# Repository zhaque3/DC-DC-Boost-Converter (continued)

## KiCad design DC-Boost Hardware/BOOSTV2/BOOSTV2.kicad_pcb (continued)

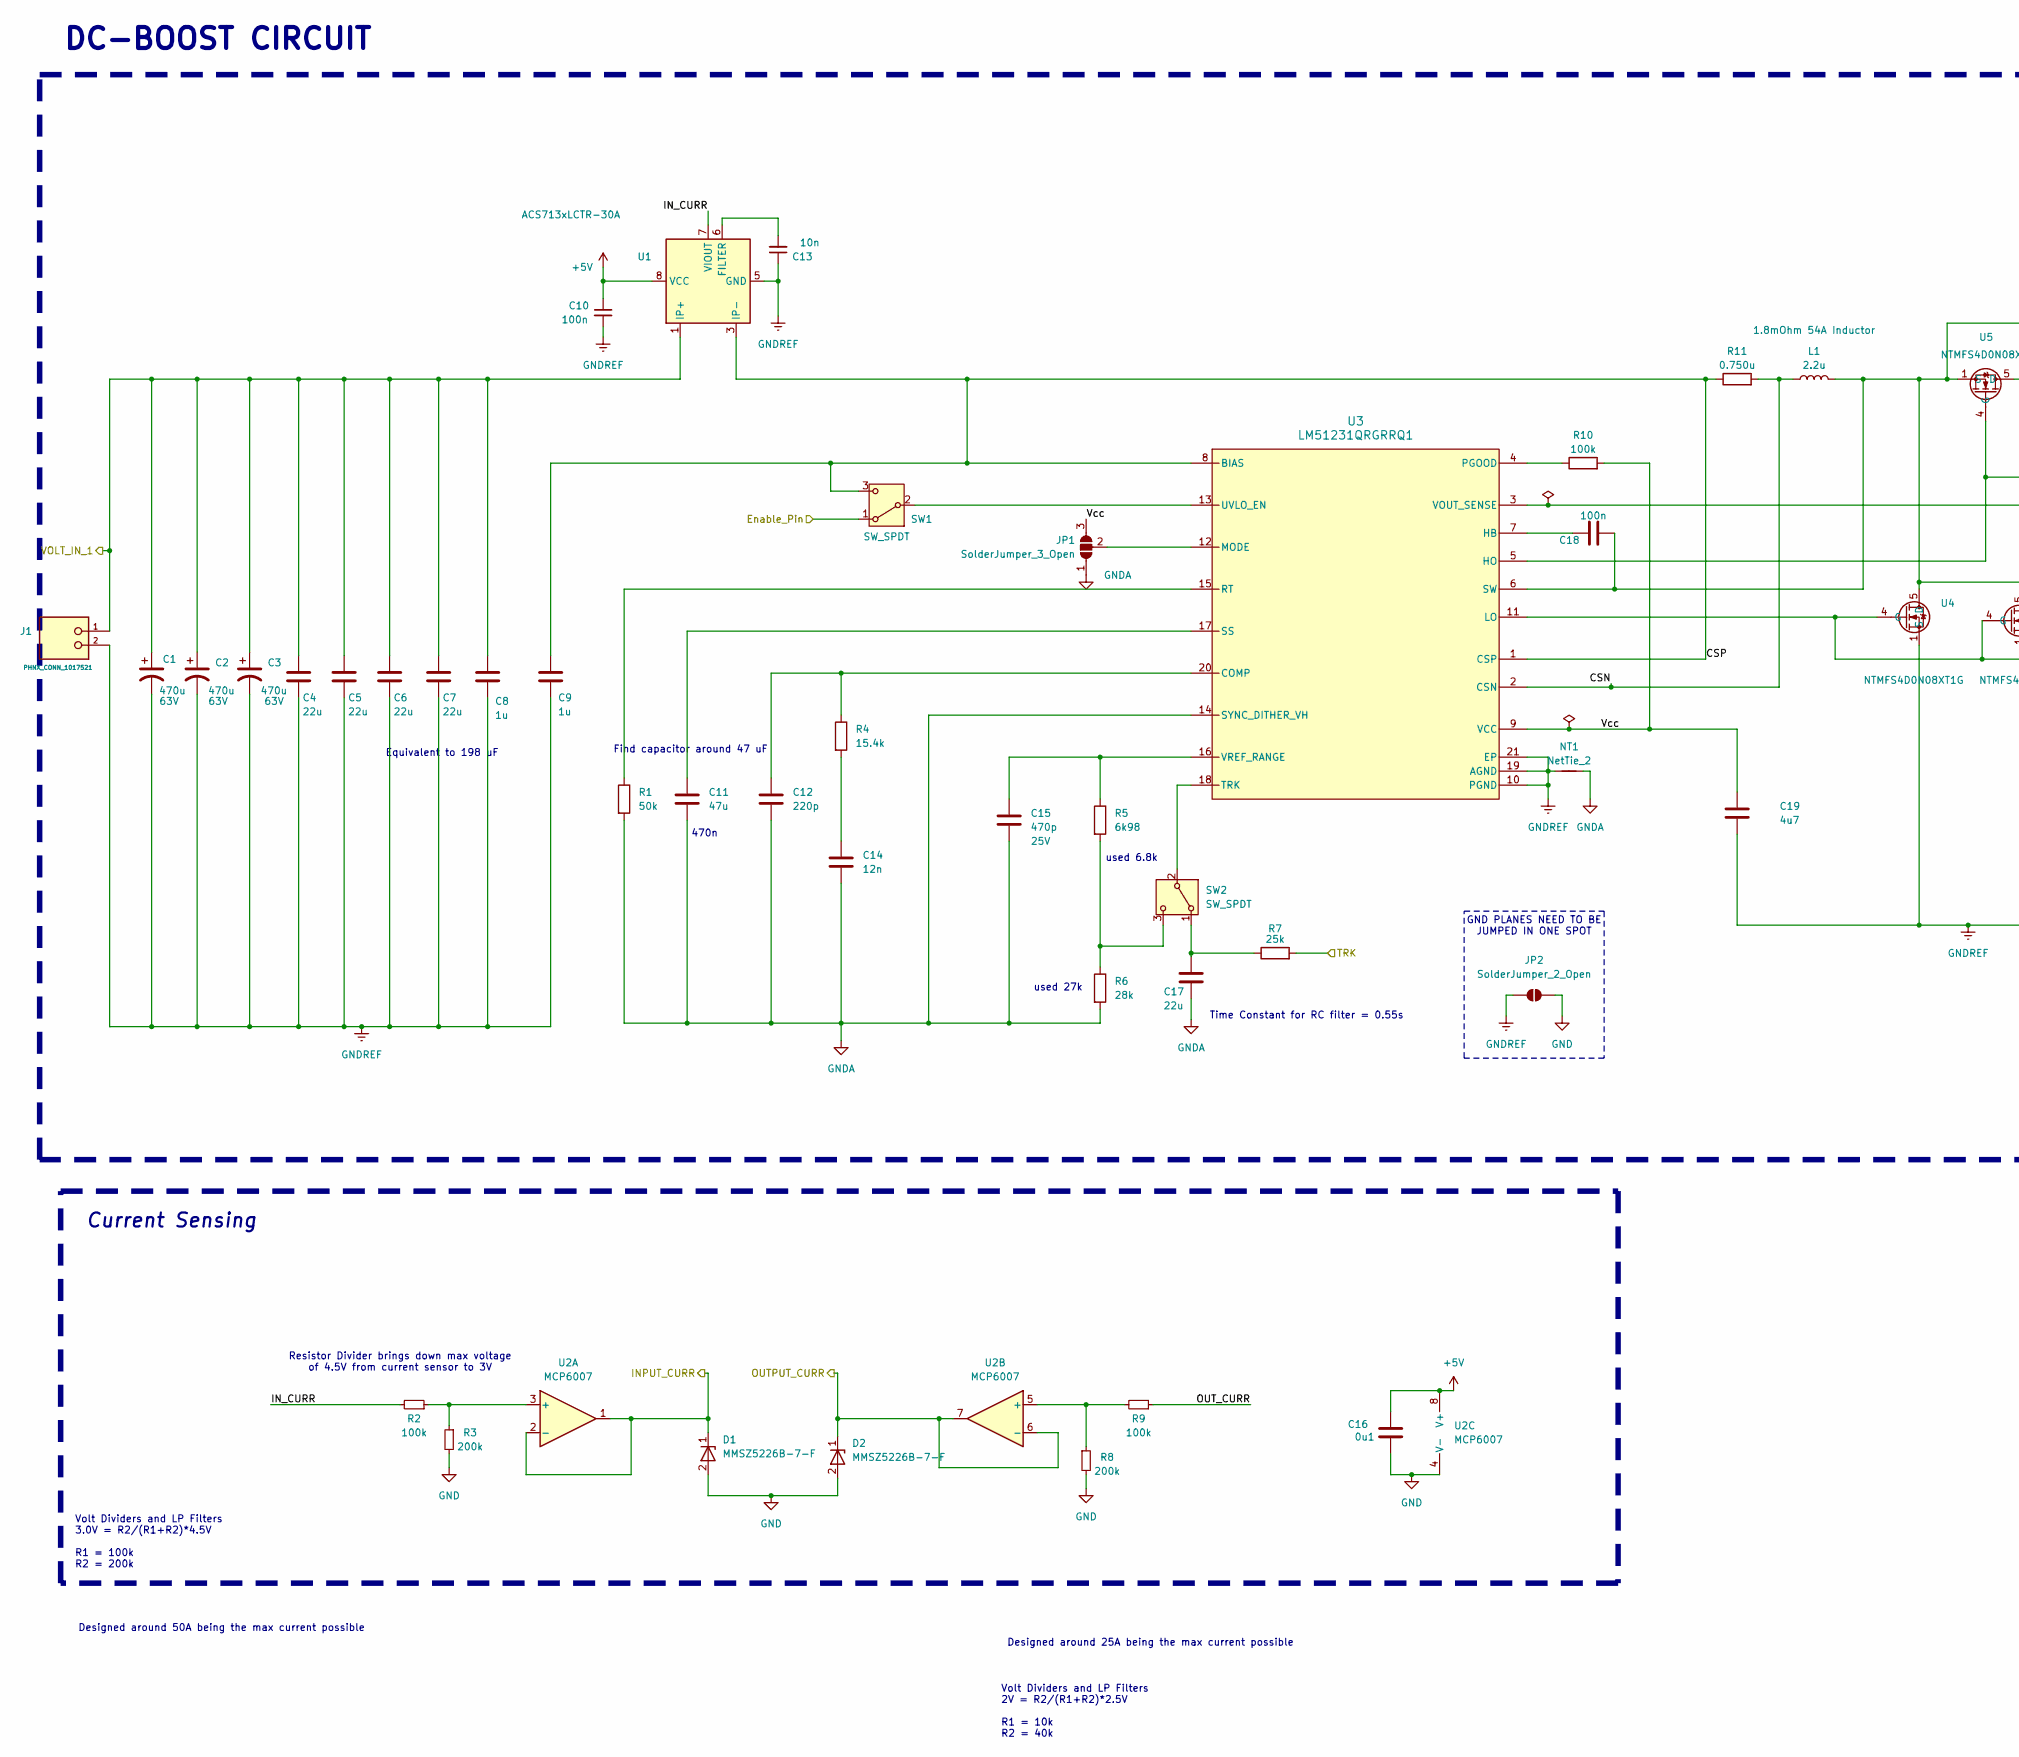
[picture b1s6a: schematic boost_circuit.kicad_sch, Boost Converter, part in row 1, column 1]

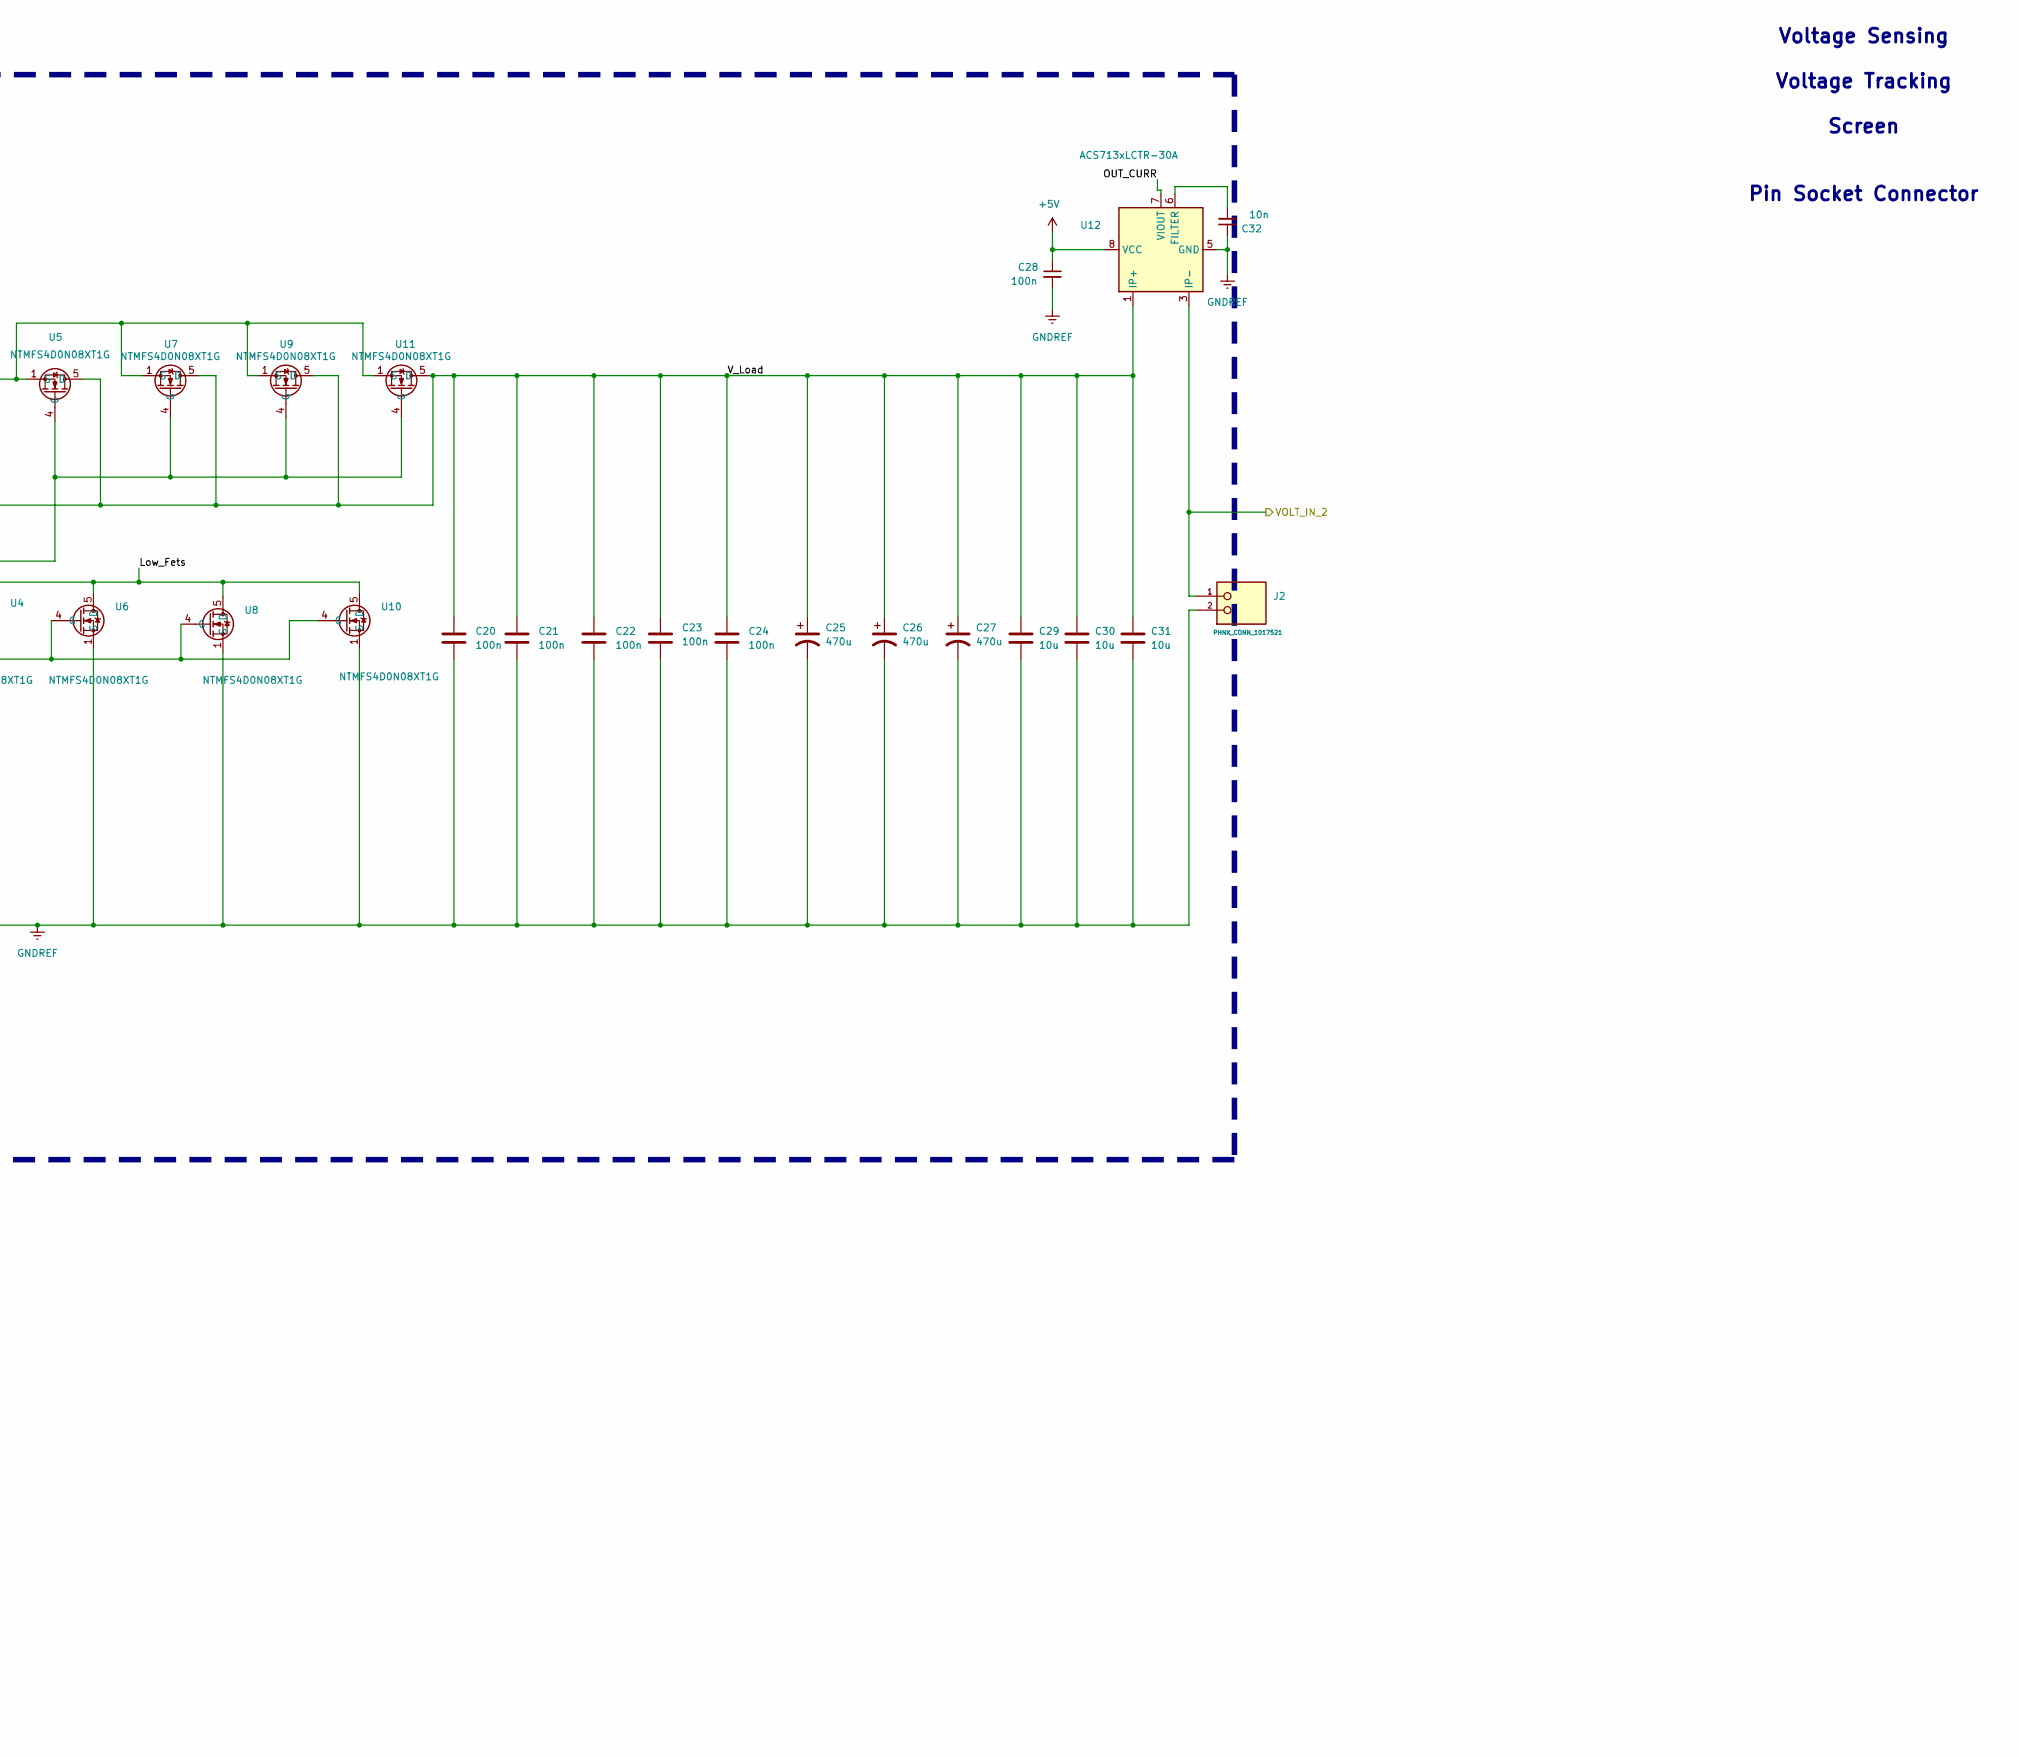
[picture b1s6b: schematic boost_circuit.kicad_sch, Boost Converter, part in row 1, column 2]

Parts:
C1, C2, C3: 470u; CAP_PAN_10X20_PAN; Part # ECA-1HM471B
C4, C5, C6, C7: 22u; C_0805_2012Metric
C8, C9: 1u; C_0603_1608Metric
C10, C28: 100n; C_0603_1608Metric; Part# C88219
C11: 47u; C_0603_1608Metric
C12: 220p; C_0805_2012Metric
C13, C32: 10n; C_0603_1608Metric; Part# C88219
C14: 12n; C_0603_1608Metric
C15: 470p; C_0603_1608Metric; Rating 25V
C16: 0u1; C_0603_1608Metric
C17: 22u; C_0603_1608Metric
C18: 100n; R_0603_1608Metric
C19: 4u7; C_0603_1608Metric
C20, C21, C22, C23, C24: 100n; C_0603_1608Metric
C25, C26, C27: 470u; CAP_YX_16X31P5_RUB; Part # 100ZLH470MEFC16X31.5
C29, C30, C31: 10u; C_1210_3225Metric
D1, D2: MMSZ5226B-7-F; D_SOD_123_M; Part# C155250
J1, J2: PHNX_CONN_1017521; PHOENIX_1017521; PARTREV 04.01.2018
JP1: SolderJumper_3_Open; SolderJumper-3_P1.3mm_Open_RoundedPad1.0x1.5mm_NumberLabels
JP2: SolderJumper_2_Open; SolderJumper-2_P1.3mm_Open_RoundedPad1.0x1.5mm
L1: 2.2u; L_Kemet_3u3
NT1: NetTie_2; NetTie-2_SMD_Pad0.5mm
R1: 50k; R_0603_1608Metric
R2, R9, R10: 100k; R_0603_1608Metric
R3: 200k; R_0603_1608Metric; Part# C25811
R4: 15.4k; R_0603_1608Metric_Pad0.98x0.95mm_HandSolder
R5: 6k98; R_0603_1608Metric
R6: 28k; R_0603_1608Metric
R7: 25k; R_0603_1608Metric
R8: 200k; R_0603_1608Metric
R11: 0.750u; CSS2H3920RL700F
SW1, SW2: SW_SPDT; PinHeader_1x03_P2.54mm_Vertical
U1, U12: ACS713xLCTR-30A; SOIC-8_3.9x4.9mm_P1.27mm
U2: MCP6007; SOIC-8_3.9x4.9mm_P1.27mm
U3: LM51231QRGRRQ1; RGR0020C-MFG
U4, U5, U6, U7, U8, U9, U10, U11: NTMFS4D0N08XT1G; PowerMosDFNHybrid

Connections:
+5V: C10.1, C16.1, C28.1, U1.8 (VCC), U2.8 (V+), U12.8 (VCC); also elsewhere on the board
/Boost-Circuit/CSN: L1.1, R11.2, U3.2 (CSN)
/Boost-Circuit/CSP: C9.1, R11.1, SW1.3 (C), U1.3 (IP-), U1.4 (IP-), U3.1 (CSP), U3.8 (BIAS)
/Boost-Circuit/Enable_Pin: SW1.1 (A); also elsewhere on the board
/Boost-Circuit/INPUT_CURR: D1.1, U2.1, U2.2 (-); also elsewhere on the board
/Boost-Circuit/IN_CURR: R2.2, U1.7 (VIOUT)
/Boost-Circuit/Low_Fets: C18.1, L1.2, U3.6 (SW), U4.5 (D), U5.1 (S), U5.2 (S), U5.3 (S), U6.5 (D), U7.1 (S), U7.2 (S), U7.3 (S), U8.5 (D), U9.1 (S), U9.2 (S), U9.3 (S), U10.5 (D), U11.1 (S), U11.2 (S), U11.3 (S)
/Boost-Circuit/OUTPUT_CURR: D2.1, U2.6 (-), U2.7; also elsewhere on the board
/Boost-Circuit/OUT_CURR: R9.1, U12.7 (VIOUT)
/Boost-Circuit/TRK: R7.2; also elsewhere on the board
/Boost-Circuit/VOLT_IN_1: C1.1, C2.1, C3.1, C4.1, C5.1, C6.1, C7.1, C8.1, J1.1, U1.1 (IP+), U1.2 (IP+); also elsewhere on the board
/Boost-Circuit/VOLT_IN_2: J2.1, U12.3 (IP-), U12.4 (IP-); also elsewhere on the board
/Boost-Circuit/V_Load: C20.1, C21.1, C22.1, C23.1, C24.1, C25.1, C26.1, C27.1, C29.1, C30.1, C31.1, U3.3 (VOUT_SENSE), U5.5 (D), U7.5 (D), U9.5 (D), U11.5 (D), U12.1 (IP+), U12.2 (IP+)
/Boost-Circuit/Vcc: C19.1, JP1.3 (B), R10.2, U3.9 (VCC)
GND: C16.2, D1.2, D2.2, JP2.2 (B), R3.2, R8.2, U2.4 (V-); also elsewhere on the board
GNDA: C11.2, C12.2, C14.2, C15.2, C17.2, JP1.1 (A), NT1.2, R1.2, R6.2, U3.14 (SYNC_DITHER_VH)
GNDREF: C1.2, C2.2, C3.2, C4.2, C5.2, C6.2, C7.2, C8.2, C9.2, C10.2, C13.1, C19.2, C20.2, C21.2, C22.2, C23.2, C24.2, C25.2, C26.2, C27.2, C28.2, C29.2, C30.2, C31.2, C32.1, J1.2, J2.2, JP2.1 (A), NT1.1, U1.5 (GND), U3.10 (PGND), U3.19 (AGND), U3.21 (EP), U4.1 (S), U4.2 (S), U4.3 (S), U6.1 (S), U6.2 (S), U6.3 (S), U8.1 (S), U8.2 (S), U8.3 (S), U10.1 (S), U10.2 (S), U10.3 (S), U12.5 (GND)
unnamed: C14.1, R4.2
unnamed: JP1.2 (C), U3.12 (MODE)
unnamed: SW1.2 (B), U3.13 (UVLO_EN)
unnamed: C17.1, R7.1, SW2.1 (A)
unnamed: SW2.2 (B), U3.18 (TRK)
unnamed: R5.2, R6.1, SW2.3 (C)
unnamed: C13.2, U1.6 (FILTER)
unnamed: R2.1, R3.1, U2.3 (+)
unnamed: R8.1, R9.2, U2.5 (+)
unnamed: C12.1, R4.1, U3.20 (COMP)
unnamed: C18.2, U3.7 (HB)
unnamed: R10.1, U3.4 (PGOOD)
unnamed: R1.1, U3.15 (RT)
unnamed: C11.1, U3.17 (SS)
unnamed: C15.1, R5.1, U3.16 (VREF_RANGE)
unnamed: U3.11 (LO), U4.4 (G), U6.4 (G), U8.4 (G), U10.4 (G)
unnamed: U3.5 (HO), U5.4 (G), U7.4 (G), U9.4 (G), U11.4 (G)
unnamed: C32.2, U12.6 (FILTER)

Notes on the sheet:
used 27k
DC-BOOST CIRCUIT
Resistor Divider brings down max voltage of 4.5V from current sensor to 3V
470n
used 6.8k
Volt Dividers and LP Filters 3.0V = R2/(R1+R2)*4.5V R1 = 100k R2 = 200k
Time Constant for RC filter = 0.55s
Volt Dividers and LP Filters 2V = R2/(R1+R2)*2.5V R1 = 10k R2 = 40k
Current Sensing
GND PLANES NEED TO BE JUMPED IN ONE SPOT
Voltage Sensing Voltage Tracking Screen Pin Socket Connector
Designed around 25A being the max current possible
Find capacitor around 47 uF
Designed around 50A being the max current possible
Equivalent to 198 uF

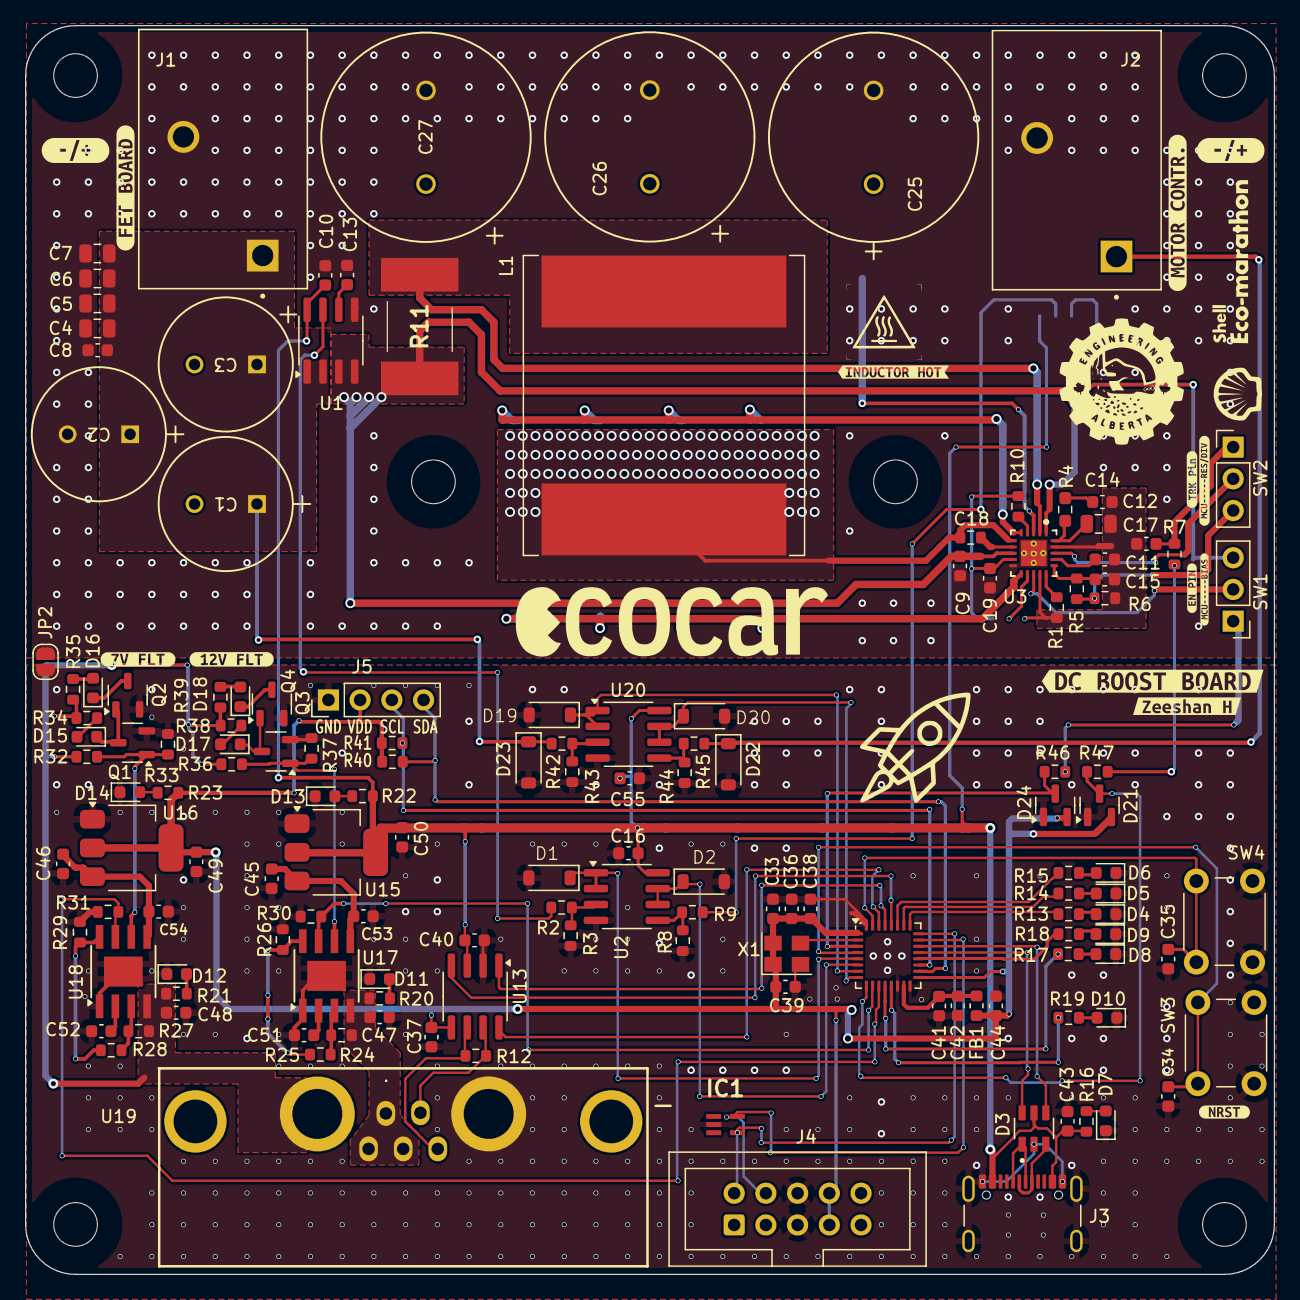
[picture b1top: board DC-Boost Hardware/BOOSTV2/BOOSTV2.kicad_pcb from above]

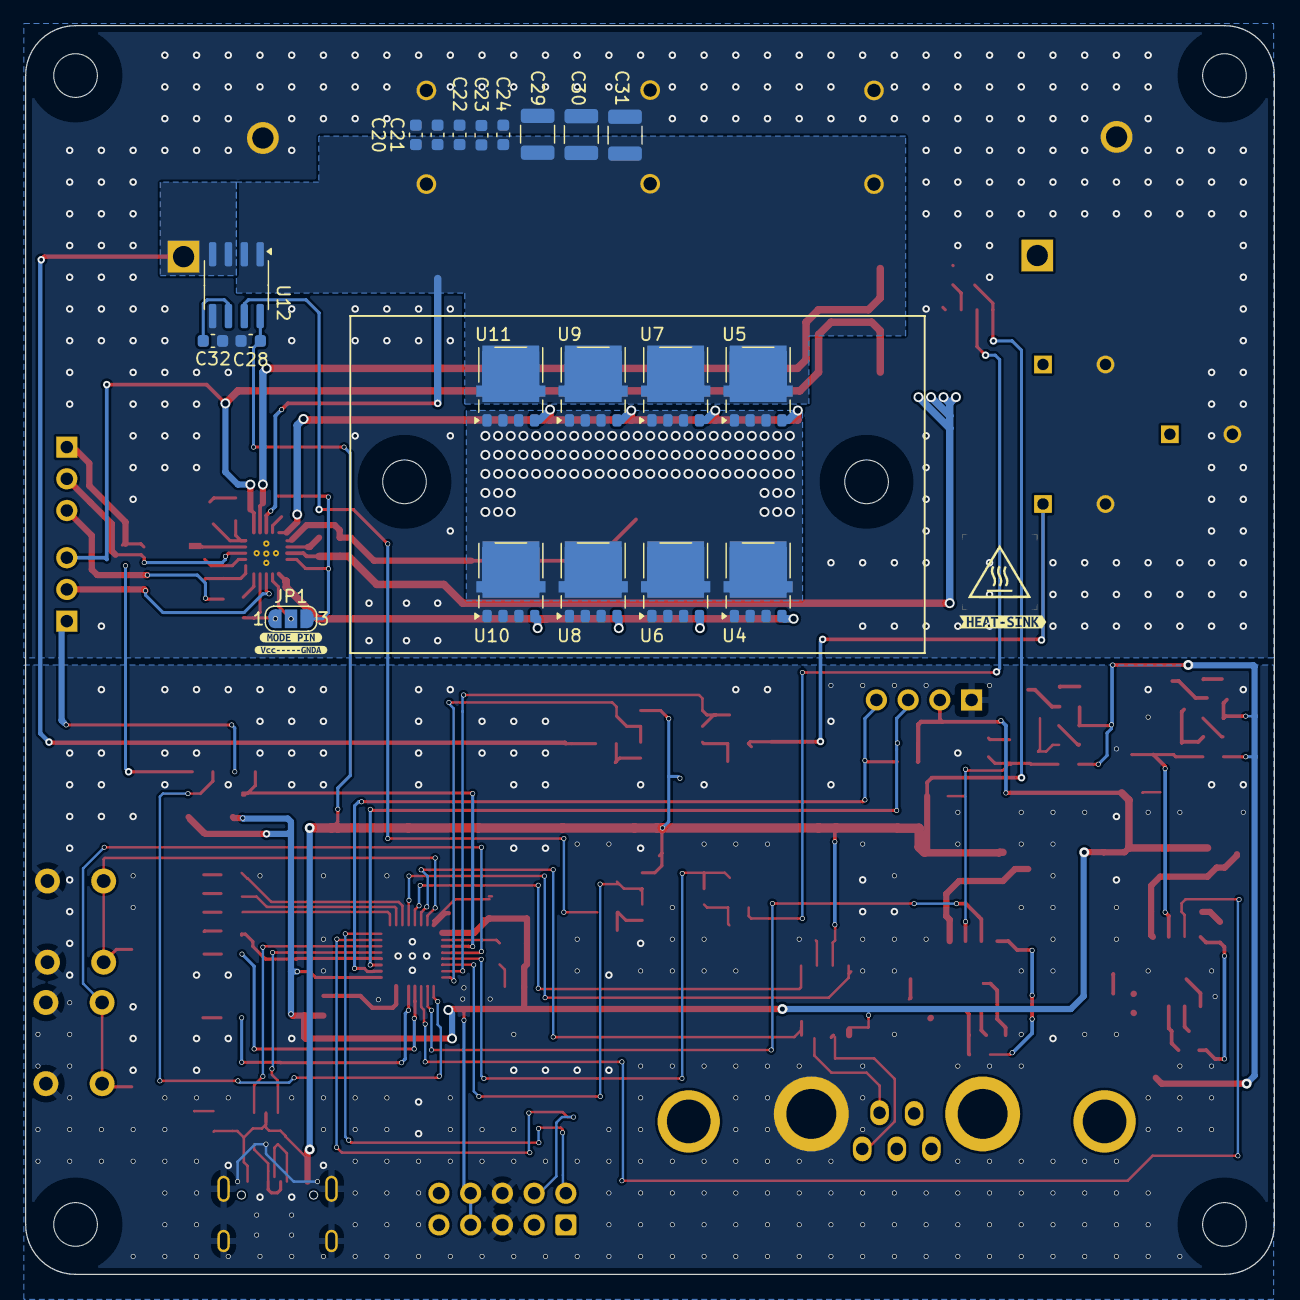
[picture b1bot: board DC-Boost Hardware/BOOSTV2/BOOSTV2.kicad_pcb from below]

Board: 2 copper layers, 100.0 x 100.0 mm, 189 parts (23 on the bottom side), 98 nets.

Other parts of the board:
kibuzzard-67B8F6AB: G***; kibuzzard-67B8F6AB
kibuzzard-67B8F68E: G***; kibuzzard-67B8F68E
kibuzzard-67B8F697: G***; kibuzzard-67B8F697
kibuzzard-67B37C45: G***; kibuzzard-67B37C45
kibuzzard-67B37DE2: G***; kibuzzard-67B37DE2
kibuzzard-67B58E6E: G***; kibuzzard-67B58E6E
kibuzzard-67B58E58: G***; kibuzzard-67B58E58
kibuzzard-67B540FD: G***; kibuzzard-67B540FD
kibuzzard-67B591A9: G***; kibuzzard-67B591A9
kibuzzard-67BA3C10: G***; kibuzzard-67BA3C10
kibuzzard-67BA360B: G***; kibuzzard-67BA360B
kibuzzard-67BA362A: G***; kibuzzard-67BA362A
kibuzzard-6743FE6D: G***; kibuzzard-6743FE6D
kibuzzard-6743FE8B: G***; kibuzzard-6743FE8B
kibuzzard-694398FD: G***; kibuzzard-694398FD
kibuzzard-67392652, kibuzzard-67392652#2: G***; kibuzzard-67392652

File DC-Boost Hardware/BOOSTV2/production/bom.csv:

Designator,Footprint,Quantity,Value,LCSC Part #
"C1, C2, C3",CAP_PAN_10X20_PAN,3,470u,
"C10, C18, C20, C21, C22, C23, C24, C28, C34, C35, C36, C37, C38, C39, C40, C43",0603,16,100n,
C11,0603,1,330n,
C12,0805,1,330p,
"C13, C32, C41",0603,3,10n,
C14,0603,1,56n,
C15,0603,1,470p,
"C16, C55",0603,2,0u1,
"C17, C49, C50",0603,3,22u,
"C19, C33",0603,2,4u7,
"C25, C26, C27",CAP_YX_16X31P5_RUB,3,470u,
"C29, C30, C31",1210,3,10u,
"C4, C5, C6, C7",0805,4,22u,
"C42, C44, C47, C48, C53, C54, C8, C9",0603,8,1u,
"C45, C46",0603,2,10u,
"C51, C52",0603,2,2n2,
"D1, D19, D2, D20",D_SOD_123_M,4,MMSZ5226B-7-F,
"D10, D15, D17, D9",0603,4,Red,
"D11, D12, D13, D14",0603,4,BLUE,
"D16, D18",0603,2,Green,
"D21, D24",SOT-23,2,BAT54S,
D22,D_SOD-123,1,MMSZ5266BT1G,
D23,D_SOD-123,1,MMSZ5257BT1G,
D3,SOT95P280X145-6N,1,USBLC6-2SC6,
"D4, D5, D6, D8",0603,4,Amber,
D7,0603,1,LED,
FB1,0603,1,300R,
IC1,SOT65P210X110-5N,1,ESDALC6V1W5,
"J1, J2",PHOENIX_1017521,2,PHNX_CONN_1017521,
J3,USB_C_Receptacle_GCT_USB4105-xx-A_16P_TopMnt_Horizontal,1,USB_C_Receptacle_USB2.0_14P,
J4,IDC-STM32-Prog-Header_2x05_P2.54mm_Vertical,1,STM32-Prog-Header,
J5,Display_128x64_096_I2C,1,OLED,
L1,L_Kemet_3u3,1,MPXV1D2213L3R3,
"Q1, Q2, Q3, Q4",SOT-23-3_Adjusted,4,SI2302A-TPMSCT-ND,
R1,0603,1,221k,
"R10, R2, R9",0603,3,100k,
R11,CSS2H3920RL700F,1,1m5,
R12,0603,1,R,
"R13, R14, R15, R17, R18, R19, R22, R23",0603,8,220R,
R16,0603,1,140R,
R20,0603,1,820,
"R21, R34, R35, R38, R39",0603,5,270,
R24,0603,1,10k,
"R25, R26, R28",0603,3,1k,
R27,0603,1,8k,
"R29, R30, R31",0603,3,1k2,
"R3, R8",0603,2,200k,
"R32, R36",0603,2,12k,
"R33, R37",0603,2,30k,
R4,0603,1,5k,
"R40, R41",0603,2,4k7,
R42,0603,1,27k,
R43,0603,1,3k,
R44,0603,1,3k6,
R45,0603,1,68k,
"R46, R47",0603,2,10,
R5,0603,1,6k98,
R6,0603,1,28k,
R7,0603,1,25k,
"SW1, SW2",PinHeader_1x03_P2.54mm_Vertical,2,SW_SPDT,
SW3,SW_PUSH_6mm_H5mm,1,RESET,
SW4,SW_PUSH_6mm_H5mm,1,GPIO,
"U1, U12",SOIC-8_3.9x4.9mm_P1.27mm,2,ACS713xLCTR-30A,
"U10, U11, U4, U5, U6, U7, U8, U9",PowerMosDFNHybrid,8,NTMFS4D0N08XT1G,
U13,SOIC-8_3.9x4.9mm_P1.27mm,1,MCP2542FD,
U14,QFN-32-1EP_5x5mm_P0.5mm_EP3.45x3.45mm,1,STM32G491KEUx,
U15,SOT-223-3_TabPin2,1,AZ1117IH-5.0,
U16,SOT-223-3_TabPin2,1,AZ1117IH-3.3,
"U17, U18",TI_SO-PowerPAD-8,2,TPS259631,
U19,DB7W2-Male,1,~,
"U2, U20",SOIC-8_3.9x4.9mm_P1.27mm,2,MCP6007,
U3,RGR0020C-MFG,1,LM51231QRGRRQ1,
X1,Crystal_SMD_3225-4Pin_3.2x2.5mm,1,OXETDLJANF-8MHZ,

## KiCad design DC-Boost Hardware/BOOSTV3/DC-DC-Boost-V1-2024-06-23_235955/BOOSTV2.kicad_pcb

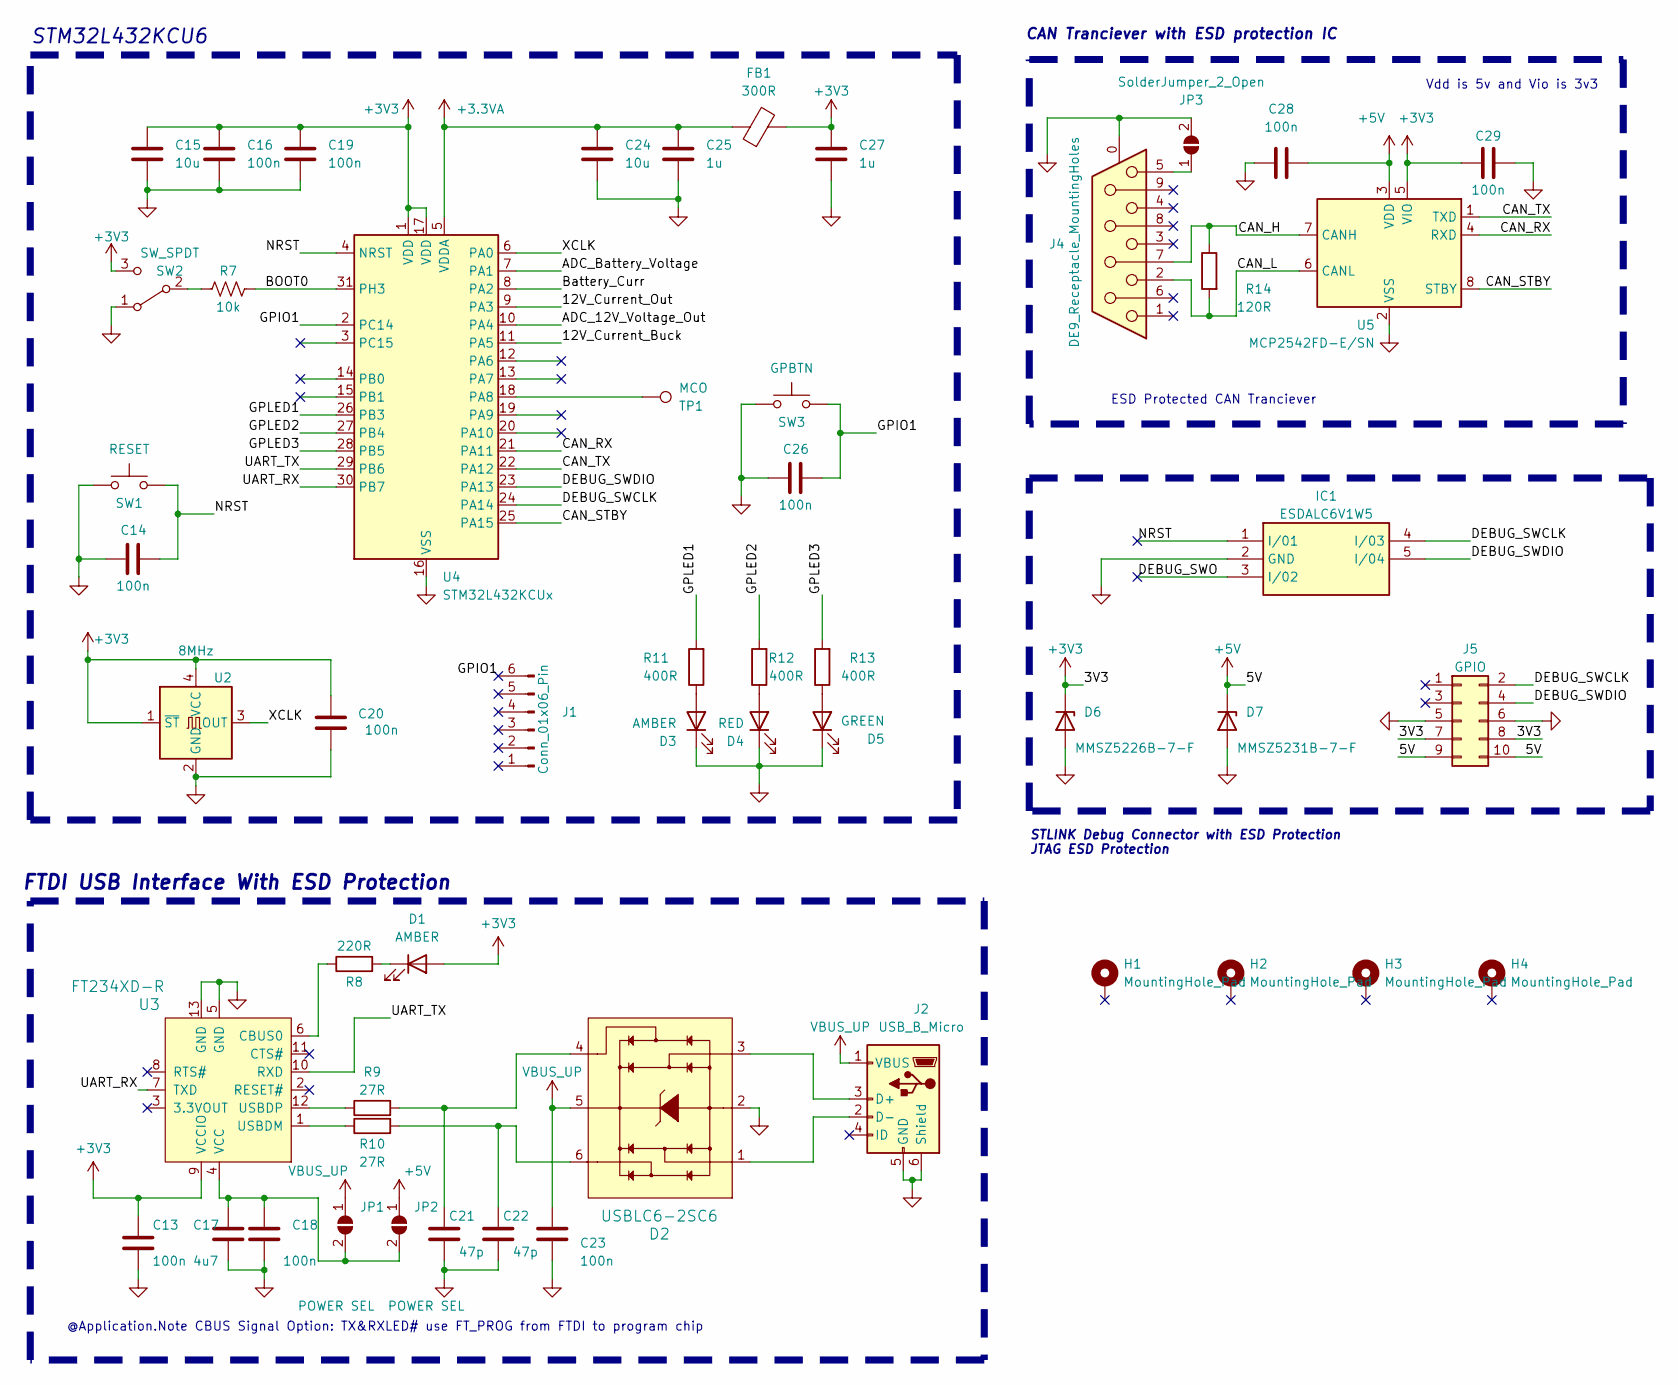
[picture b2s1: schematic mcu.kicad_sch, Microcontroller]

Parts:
C13, C14, C16, C18, C19, C20, C23, C26, C28, C29: 100n; C_0402_1005Metric; JLCPCB Part#(Optional) C1525
C15, C24: 10u; C_0603_1608Metric; JLCPCB Part#(Optional) C96446
C17: 4u7; C_0603_1608Metric; JLCPCB Part#(Optional) C1779
C21, C22: 47p; C_0402_1005Metric; JLCPCB Part#(Optional) C1671
C25, C27: 1u; C_0603_1608Metric; JLCPCB Part#(Optional) C28323
D1, D3: AMBER; LED_0805_2012Metric; JLCPCB Part#(Optional) C2296
D2: USBLC6-2SC6; SOT95P280X145-6N; Digikey # 497-5235-1-ND
D4: RED; LED_0805_2012Metric; JLCPCB Part#(Optional) C84256
D5: GREEN; LED_0805_2012Metric; JLCPCB Part#(Optional) C2297
D6: MMSZ5226B-7-F; D_SOD-123; Digikey # MMSZ5226B-FDICT-ND
D7: MMSZ5231B-7-F; D_SOD-123; Digikey # MMSZ5231B-7-F
FB1: 300R; L_0603_1608Metric; Digikey # 1934-1474-1-ND
H1, H2, H3, H4: MountingHole_Pad; MountingHole_3.2mm_M3_Pad
IC1: ESDALC6V1W5; SOT65P210X110-5N; JLCPCB Part#(Optional) C2827626
J1: Conn_01x06_Pin; PinHeader_2x03_P2.54mm_Vertical
J2: USB_B_Micro; USB_Micro-B_Amphenol_10118194_Horizontal; Digikey # 609-4618-1-ND
J4: DE9_Receptacle_MountingHoles; DSUB-9_Female_Horizontal_P2.77x2.84mm_EdgePinOffset7.70mm_H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
J5: GPIO; PinHeader_2x05_P2.54mm_Vertical; JLCPCB Part#(Optional) C5116482
JP1, JP2: POWER SEL; SolderJumper-2_P1.3mm_Open_TrianglePad1.0x1.5mm
JP3: SolderJumper_2_Open; SolderJumper-2_P1.3mm_Open_RoundedPad1.0x1.5mm
R7: 10k; R_0805_2012Metric; JLCPCB Part#(Optional) C17414
R8: 220R; R_0805_2012Metric; JLCPCB Part#(Optional) C17557
R9, R10: 27R; R_0402_1005Metric; JLCPCB Part#(Optional) C25190
R11, R12, R13: 400R; R_0805_2012Metric; JLCPCB Part#(Optional) C17655
R14: 120R; R_0603_1608Metric
SW1: RESET; SW_PUSH_6mm_H5mm
SW2: SW_SPDT; SW_SPDT_PCM12; Digikey # 2223-SLW-66527511-SMT-TRCT-ND
SW3: GPBTN; SW_PUSH_6mm_H5mm
TP1: MCO; TestPoint_Pad_D1.0mm
U2: 8MHz; Crystal_SMD_3225-4Pin_3.2x2.5mm; Digikey # 535-ASE-8.000MHZ-L-C-TCT-ND
U3: FT234XD-R; SON45P300X300X80-13N; JLCPCB Part#(Optional) C132158
U4: STM32L432KCUx; QFN-32-1EP_5x5mm_P0.5mm_EP3.45x3.45mm; JLCPCB Part#(Optional) C1337280
U5: MCP2542FD-E/SN; SOIC-8_3.9x4.9mm_P1.27mm; Digikey # MCP2542FD-E/SN-ND

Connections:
+3.3VA: C24.1, C25.1, FB1.1, U4.5 (VDDA)
+3V3: C13.1, C15.1, C16.1, C19.1, C20.2, C27.1, C29.2, D1.2 (A), D6.1 (K), FB1.2, J5.7, J5.8, SW2.3 (C), U2.1 (~ST), U2.4 (VCC), U3.9 (VCCIO), U4.1 (VDD), U4.17 (VDD), U5.5 (VIO)
+5V: C28.2, D7.1 (K), J5.9, J5.10, JP2.1 (A), U5.3 (VDD)
/MCU/12V_Current_Buck: U4.11 (PA5)
/MCU/12V_Current_Out: U4.9 (PA3)
/MCU/ADC_12V_Voltage_Out: U4.10 (PA4)
/MCU/ADC_Battery_Voltage: U4.7 (PA1)
/MCU/BOOT0: R7.2, U4.31 (PH3)
/MCU/Battery_Curr: U4.8 (PA2)
/MCU/CAN_H: J4.7, R14.1, U5.7 (CANH)
/MCU/CAN_L: J4.2, R14.2, U5.6 (CANL)
/MCU/CAN_RX: U4.21 (PA11), U5.4 (RXD)
/MCU/CAN_STBY: U4.25 (PA15), U5.8 (STBY)
/MCU/CAN_TX: U4.22 (PA12), U5.1 (TXD)
/MCU/DEBUG_SWCLK: IC1.4 (I/03), J5.2, U4.24 (PA14)
/MCU/DEBUG_SWDIO: IC1.5 (I/04), J5.4, U4.23 (PA13)
/MCU/DEBUG_SWO: IC1.3 (I/02)
/MCU/GPIO1: C26.2, J1.6, SW3.2, U4.2 (PC14)
/MCU/GPLED1: R11.2, U4.26 (PB3)
/MCU/GPLED2: R12.2, U4.27 (PB4)
/MCU/GPLED3: R13.2, U4.28 (PB5)
/MCU/NRST: C14.2, IC1.1 (I/01), SW1.2, U4.4 (NRST)
/MCU/UART_RX: U3.7 (TXD), U4.30 (PB7)
/MCU/UART_TX: U3.10 (RXD), U4.29 (PB6)
/MCU/XCLK: U2.3 (OUT), U4.6 (PA0)
GND: C13.2, C14.1, C15.2, C16.2, C17.2, C18.2, C19.2, C20.1, C21.1, C22.1, C23.1, C24.2, C25.2, C26.1, C27.2, C28.1, C29.1, D2.2, D3.1 (K), D4.1 (K), D5.1 (K), D6.2 (A), D7.2 (A), IC1.2 (GND), J2.5 (GND), J2.6 (Shield), J4.0 (PAD), J5.5, J5.6, JP3.2 (B), SW1.1, SW2.1 (A), SW3.1, U2.2 (GND), U3.5 (GND), U3.13 (GND), U4.16 (VSS), U4.32 (VSS), U4.33 (VSS), U5.2 (VSS), U5.9 (VSS); also elsewhere on the board
unnamed: C21.2, D2.4, R9.2
unnamed: C22.2, D2.6, R10.2
unnamed: D1.1 (K), R8.2
unnamed: D3.2 (A), R11.1
unnamed: D4.2 (A), R12.1
unnamed: D5.2 (A), R13.1
unnamed: D2.3, J2.3 (D+)
unnamed: D2.1, J2.2 (D-)
unnamed: C17.1, C18.1, JP1.2 (B), JP2.2 (B), U3.4 (VCC)
unnamed: J4.5, JP3.1 (A)
unnamed: R7.1, SW2.2 (B)
unnamed: R8.1, U3.6 (CBUS0)
unnamed: R10.1, U3.1 (USBDM)
unnamed: R9.1, U3.12 (USBDP)
unnamed: TP1.1, U4.18 (PA8)
VBUS_UP: C23.2, D2.5, J2.1 (VBUS), JP1.1 (A)

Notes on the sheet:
@Application.Note CBUS Signal Option: TX&RXLED# use FT_PROG from FTDI to program chip
ESD Protected CAN Tranciever
Vdd is 5v and Vio is 3v3
STM32L432KCU6
CAN Tranciever with ESD protection IC
FTDI USB Interface With ESD Protection
STLINK Debug Connector with ESD Protection JTAG ESD Protection

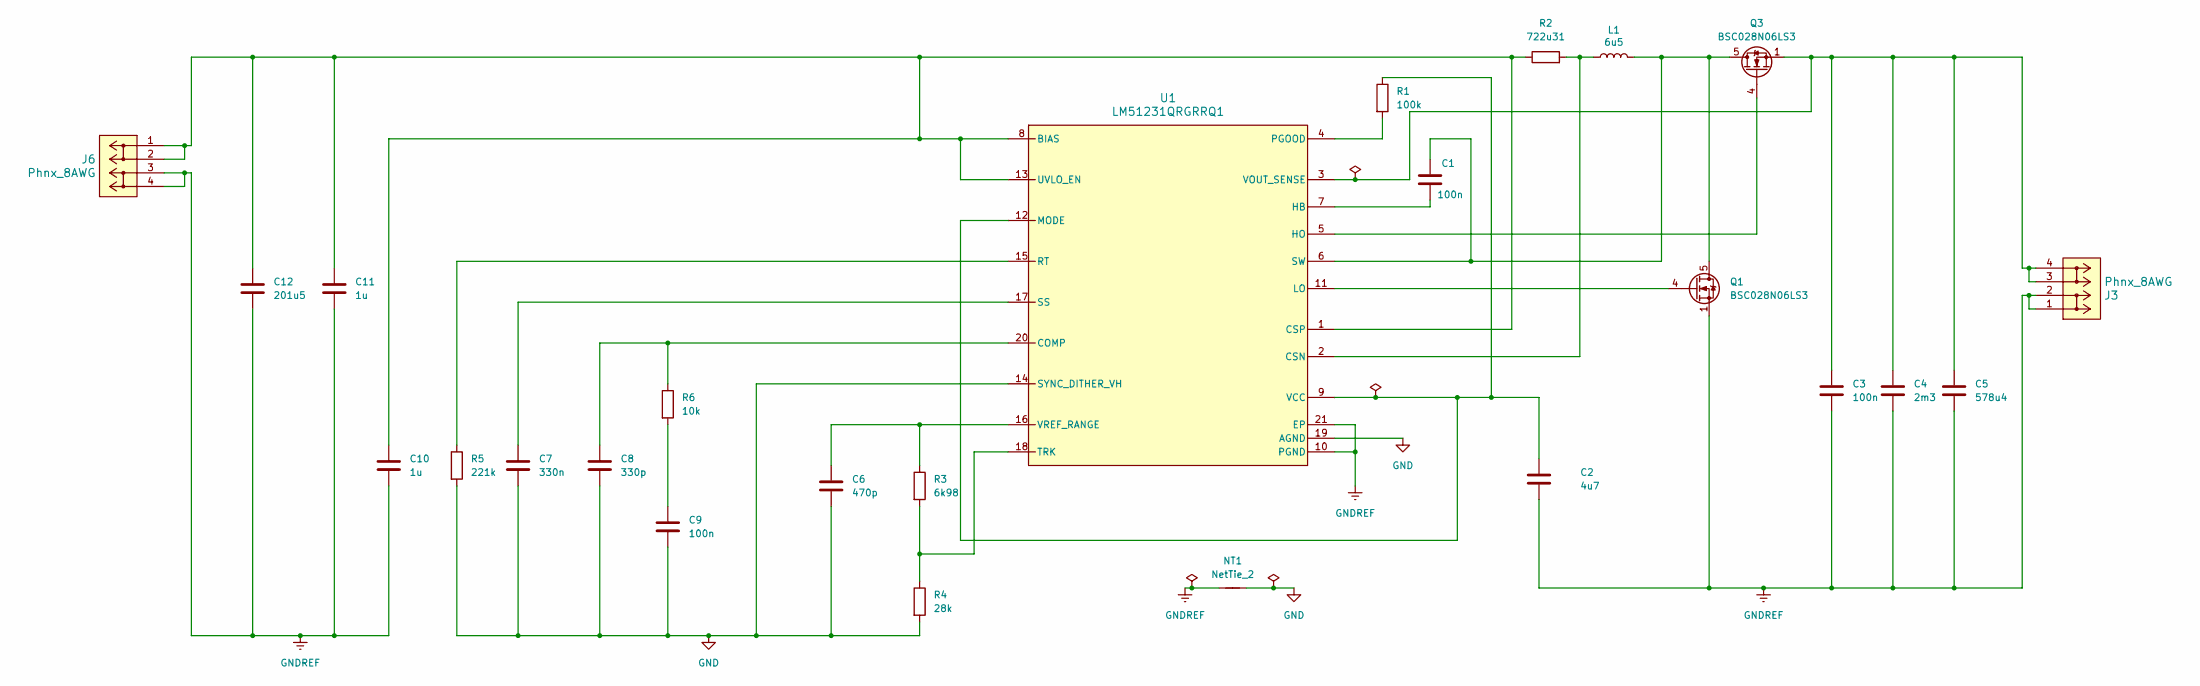
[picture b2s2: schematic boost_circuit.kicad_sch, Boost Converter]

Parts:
C1, C3, C9: 100n; C_0402_1005Metric
C2: 4u7; C_0402_1005Metric
C4: 2m3; CP_Radial_D18.0mm_P7.50mm
C5: 578u4; CAPPRD500W85D1250H3700
C6: 470p; C_0402_1005Metric
C7: 330n; C_0603_1608Metric
C8: 330p; C_0805_2012Metric
C10: 1u; C_0603_1608Metric
C11: 1u; C_0402_1005Metric
C12: 201u5; CAP_EEE1HA221P
J3, J6: Phnx_8AWG; CONN_VP0265x4xxxxG_AMP; Part# VP0265540000G-ND
L1: 6u5; L_Bourns_SRR1208_12.7x12.7mm
NT1: NetTie_2
Q1, Q3: BSC028N06LS3; TDSON-8-1
R1: 100k; R_0603_1608Metric
R2: 722u31; CSS2H3920RL700F
R3: 6k98; R_0402_1005Metric
R4: 28k; R_0402_1005Metric
R5: 221k; R_0603_1608Metric
R6: 10k; R_0201_0603Metric
U1: LM51231QRGRRQ1; RGR0020C-MFG

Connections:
GND: C6.2, C7.2, C8.2, C9.2, NT1.2, R4.2, R5.2, U1.14 (SYNC_DITHER_VH), U1.19 (AGND); also elsewhere on the board
GNDREF: C2.2, C3.2, C4.2, C5.2, C10.2, C11.2, C12.2, J3.1, J3.2, J6.3, J6.4, NT1.1, Q1.1 (S), Q1.2 (S), Q1.3 (S), U1.10 (PGND), U1.21 (EP)
unnamed: C9.1, R6.2
unnamed: C1.1, L1.2, Q1.5 (D), Q3.5 (D), U1.6 (SW)
unnamed: Q1.4 (G), U1.11 (LO)
unnamed: Q3.4 (G), U1.5 (HO)
unnamed: C10.1, C11.1, C12.1, J6.1, J6.2, R2.1, U1.1 (CSP), U1.8 (BIAS), U1.13 (UVLO_EN)
unnamed: C8.1, R6.1, U1.20 (COMP)
unnamed: L1.1, R2.2, U1.2 (CSN)
unnamed: C1.2, U1.7 (HB)
unnamed: C2.1, R1.1, U1.9 (VCC), U1.12 (MODE)
unnamed: R1.2, U1.4 (PGOOD)
unnamed: R5.1, U1.15 (RT)
unnamed: C7.1, U1.17 (SS)
unnamed: R3.2, R4.1, U1.18 (TRK)
unnamed: C3.1, C4.1, C5.1, J3.3, J3.4, Q3.1 (S), Q3.2 (S), Q3.3 (S), U1.3 (VOUT_SENSE)
unnamed: C6.1, R3.1, U1.16 (VREF_RANGE)

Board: 2 copper layers, 77 parts (0 on the bottom side), 52 nets, no tracks yet.

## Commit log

2025-11-13 made repo
2025-11-14 Initialize README with project details and guidelines
    Added detailed project description, features, and usage instructions for the DC Boost Board.
2025-12-18 Fix minor grammatical error in README purpose section
2025-12-18 README update
    Updated project details and functionality descriptions in README.md.
2025-12-18 README update
    Updated formatting and corrected spacing in the README.
2025-12-18 README update
    Removed sections on electrical design, calibration, and safety.
2025-12-18 README update
2025-12-18 README update
    Updated README.md to refine task descriptions and improve clarity.
2025-12-18 added images
    Added images to enhance project documentation.
2025-12-18 Improve image display in README.md
    Updated image formatting in README for better display.
2025-12-18 Modify images in README for better visibility
    Updated image sizes and added additional images to the README.
2025-12-18 Update README to remove unnecessary images
    Removed two image elements from the README.
